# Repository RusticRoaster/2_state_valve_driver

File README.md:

2_state_valve_driver
====================

2 state valve driver    
Author: Stan Gardner Copyright (c) 2013, All rights reserved  
Creative Commons BY license  
http://creativecommons.org/licenses/by/3.0/  

Disclamer:  
THE DOCUMENTS are PROVIDED "AS IS", WITHOUT WARRANTY OF ANY KIND, EXPRESS OR IMPLIED, 
INCLUDING BUT NOT LIMITED TO THE WARRANTIES OF MERCHANTABILITY, FITNESS FOR A PARTICULAR PURPOSE 
AND NONINFRINGEMENT. IN NO EVENT SHALL THE AUTHORS OR COPYRIGHT HOLDERS BE LIABLE FOR ANY CLAIM, 
DAMAGES OR OTHER LIABILITY, WHETHER IN AN ACTION OF CONTRACT, TORT OR OTHERWISE, ARISING FROM, 
OUT OF OR IN CONNECTION WITH THE DOCUMENTS OR THE USE OR OTHER DEALINGS IN THE DOCUMENTS.

Design came from these discussion threads.  
http://www.homeroasters.org/php/forum/viewthread.php?thread_id=3274&pid=42742#post_42742  
http://www.homeroasters.org/php/forum/viewthread.php?thread_id=3506&pid=45431#post_45431

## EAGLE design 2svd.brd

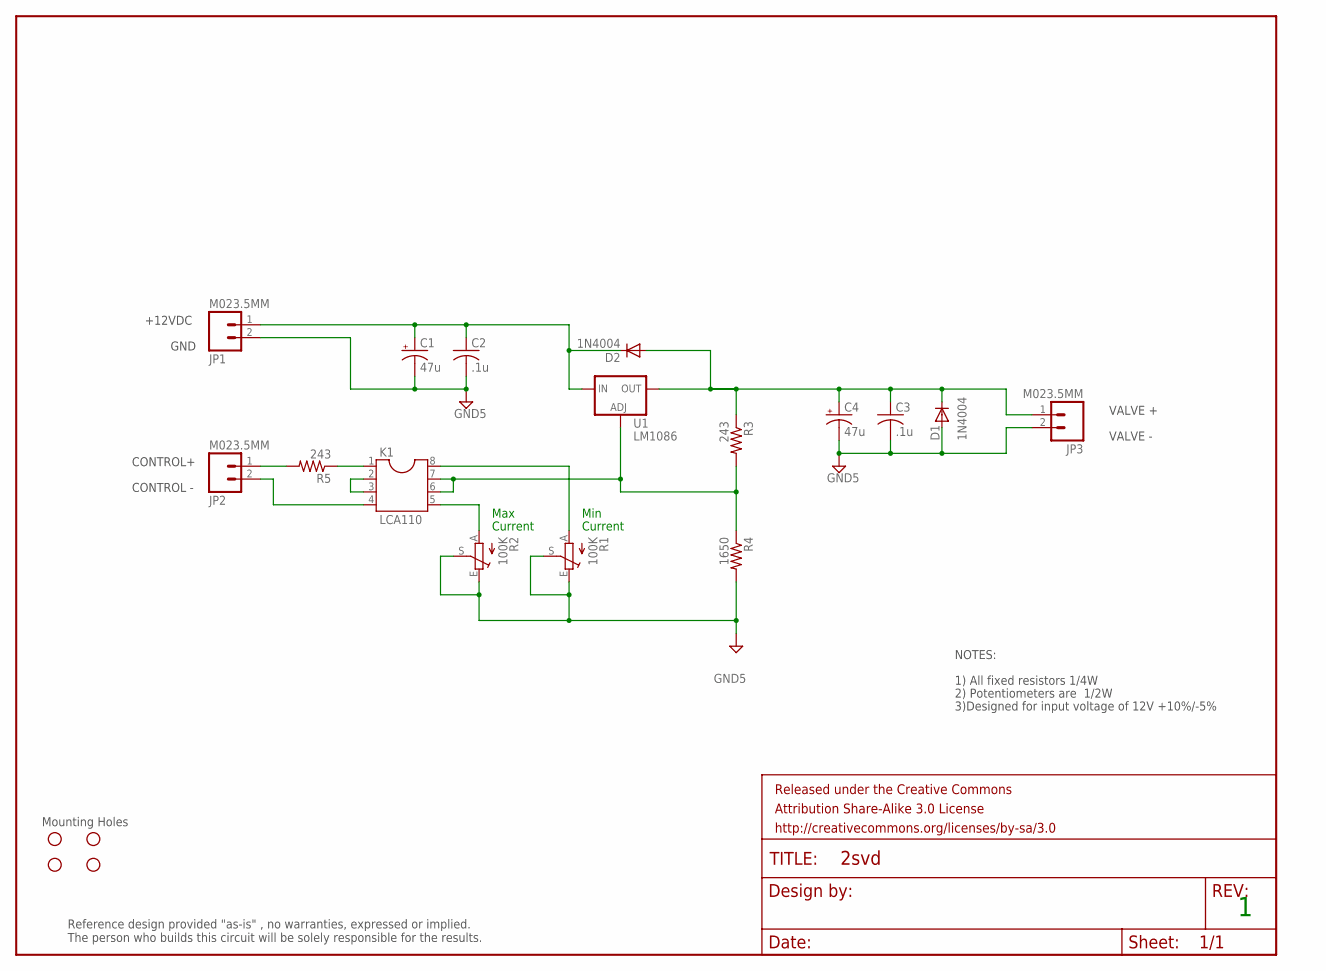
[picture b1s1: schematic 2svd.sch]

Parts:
C1, C4: 47u; CPOL-RADIAL-10UF-25V
C2, C3: .1u; C075-032X103
D1, D2: 1N4004; DO41-10
FRAME1: FRAME-LETTER; CREATIVE_COMMONS
H1, H2, H3, H4: STAND-OFF
JP1, JP2, JP3: M023.5MM; SCREWTERMINAL-3.5MM-2
K1: LCA110; DIL08
R1, R2: 100K; RJ9W
R3, R5: 243; 0207/10
R4: 1650; 0207/10
U1: LM1086; 317TS

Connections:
unnamed: K1.6, K1.7, R3.2, R4.1, U1.1 (ADJ)
unnamed: C3.1, C4.1 (+), D1.C, D2.A, JP3.1, R3.1, U1.2 (OUT)
unnamed: K1.5, R2.A
unnamed: K1.8, R1.A
unnamed: K1.1, R5.1
unnamed: K1.2, K1.3
unnamed: JP2.2, K1.4
unnamed: C1.1 (+), C2.1, D2.C, JP1.1, U1.3 (IN)
unnamed: JP2.1, R5.2
PE: C1.2 (-), C2.2, C3.2, C4.2 (-), D1.A, JP1.2, JP3.2, R1.E, R1.S, R2.E, R2.S, R4.2

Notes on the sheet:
Mounting Holes
Min
Max
Current
+12VDC
GND
CONTROL+
CONTROL -
VALVE +
VALVE -
NOTES:
1) All fixed resistors 1/4W
2) Potentiometers are 1/2W
3)Designed for input voltage of 12V +10%/-5%
Reference design provided "as-is" , no warranties, expressed or implied. The person who builds this circuit will be solely responsible for the results.

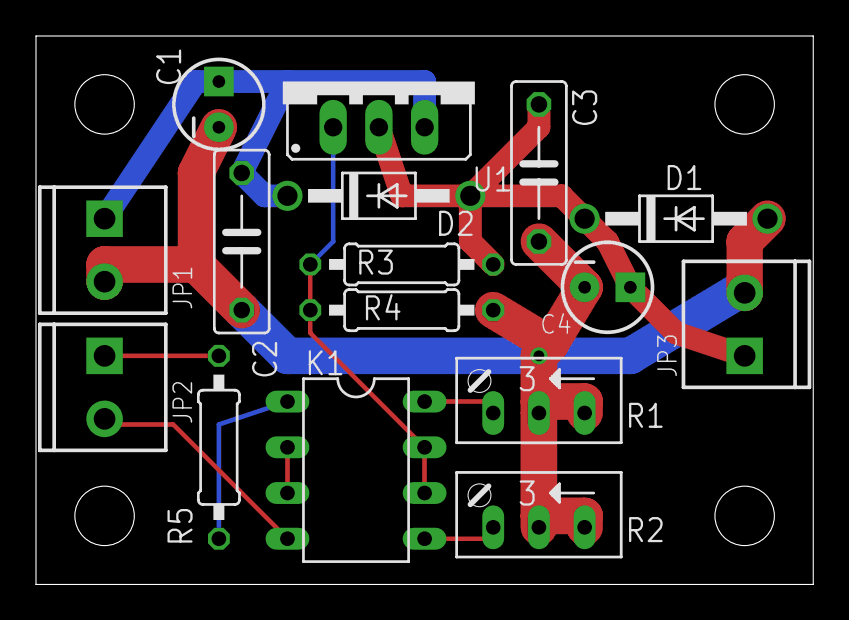
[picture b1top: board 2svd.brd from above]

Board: 2 copper layers, 43.2 x 30.5 mm, 22 parts (0 on the bottom side), 10 nets.

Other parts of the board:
DRILEGEND: DRILEGEND

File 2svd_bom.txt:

Parts list with Digikey Part numbers
C1 47u P5181-ND
C2 .1u 399-4491-1-ND
C3 .1u 399-4491-1-ND
C4 47u P5181-ND
D1 1N4004 1N4004DICT-ND
D2 1N4004 1N4004DICT-ND
K1 LBA110 CLA104-ND
R1 100K T93YA-100K-ND
R2 100K T93YA-100K-ND
R3 243 243XBK-ND
R4 1650 1.65KXBK-ND
R5 243 243XBK-ND
U1 LM1086 LM1086CT-ADJ/NOPB-ND
JP1 2POS 3.5MM 277-1721-ND
JP2 2POS 3.5MM 277-1721-ND
JP3 2POS 3.5MM 277-1721-ND

2,P5181-ND,c1 C4
2,399-4491-1-ND, c2 c3
2,1N4004DICT-ND, D1 D2
1,CLA104-ND,K1
2,T93YA-100K-ND, R1 R2
2,243XBK-ND, R3 R5
1,1.65KXBK-ND, R4
1,LM1086CT-ADJ/NOPB-ND, U1
3,277-1721-ND, JP1 JP2 JP3

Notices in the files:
parts and their libraries:
SparkFun-Electromechanical: Licensing: CC v3.0 Share-Alike You are welcome to use this library for commercial purposes.
SparkFun-Aesthetics: Released under the Creative Commons Attribution Share-Alike 3.0 License
SparkFun-Aesthetics: http://creativecommons.org/licenses/by-sa/3.0
